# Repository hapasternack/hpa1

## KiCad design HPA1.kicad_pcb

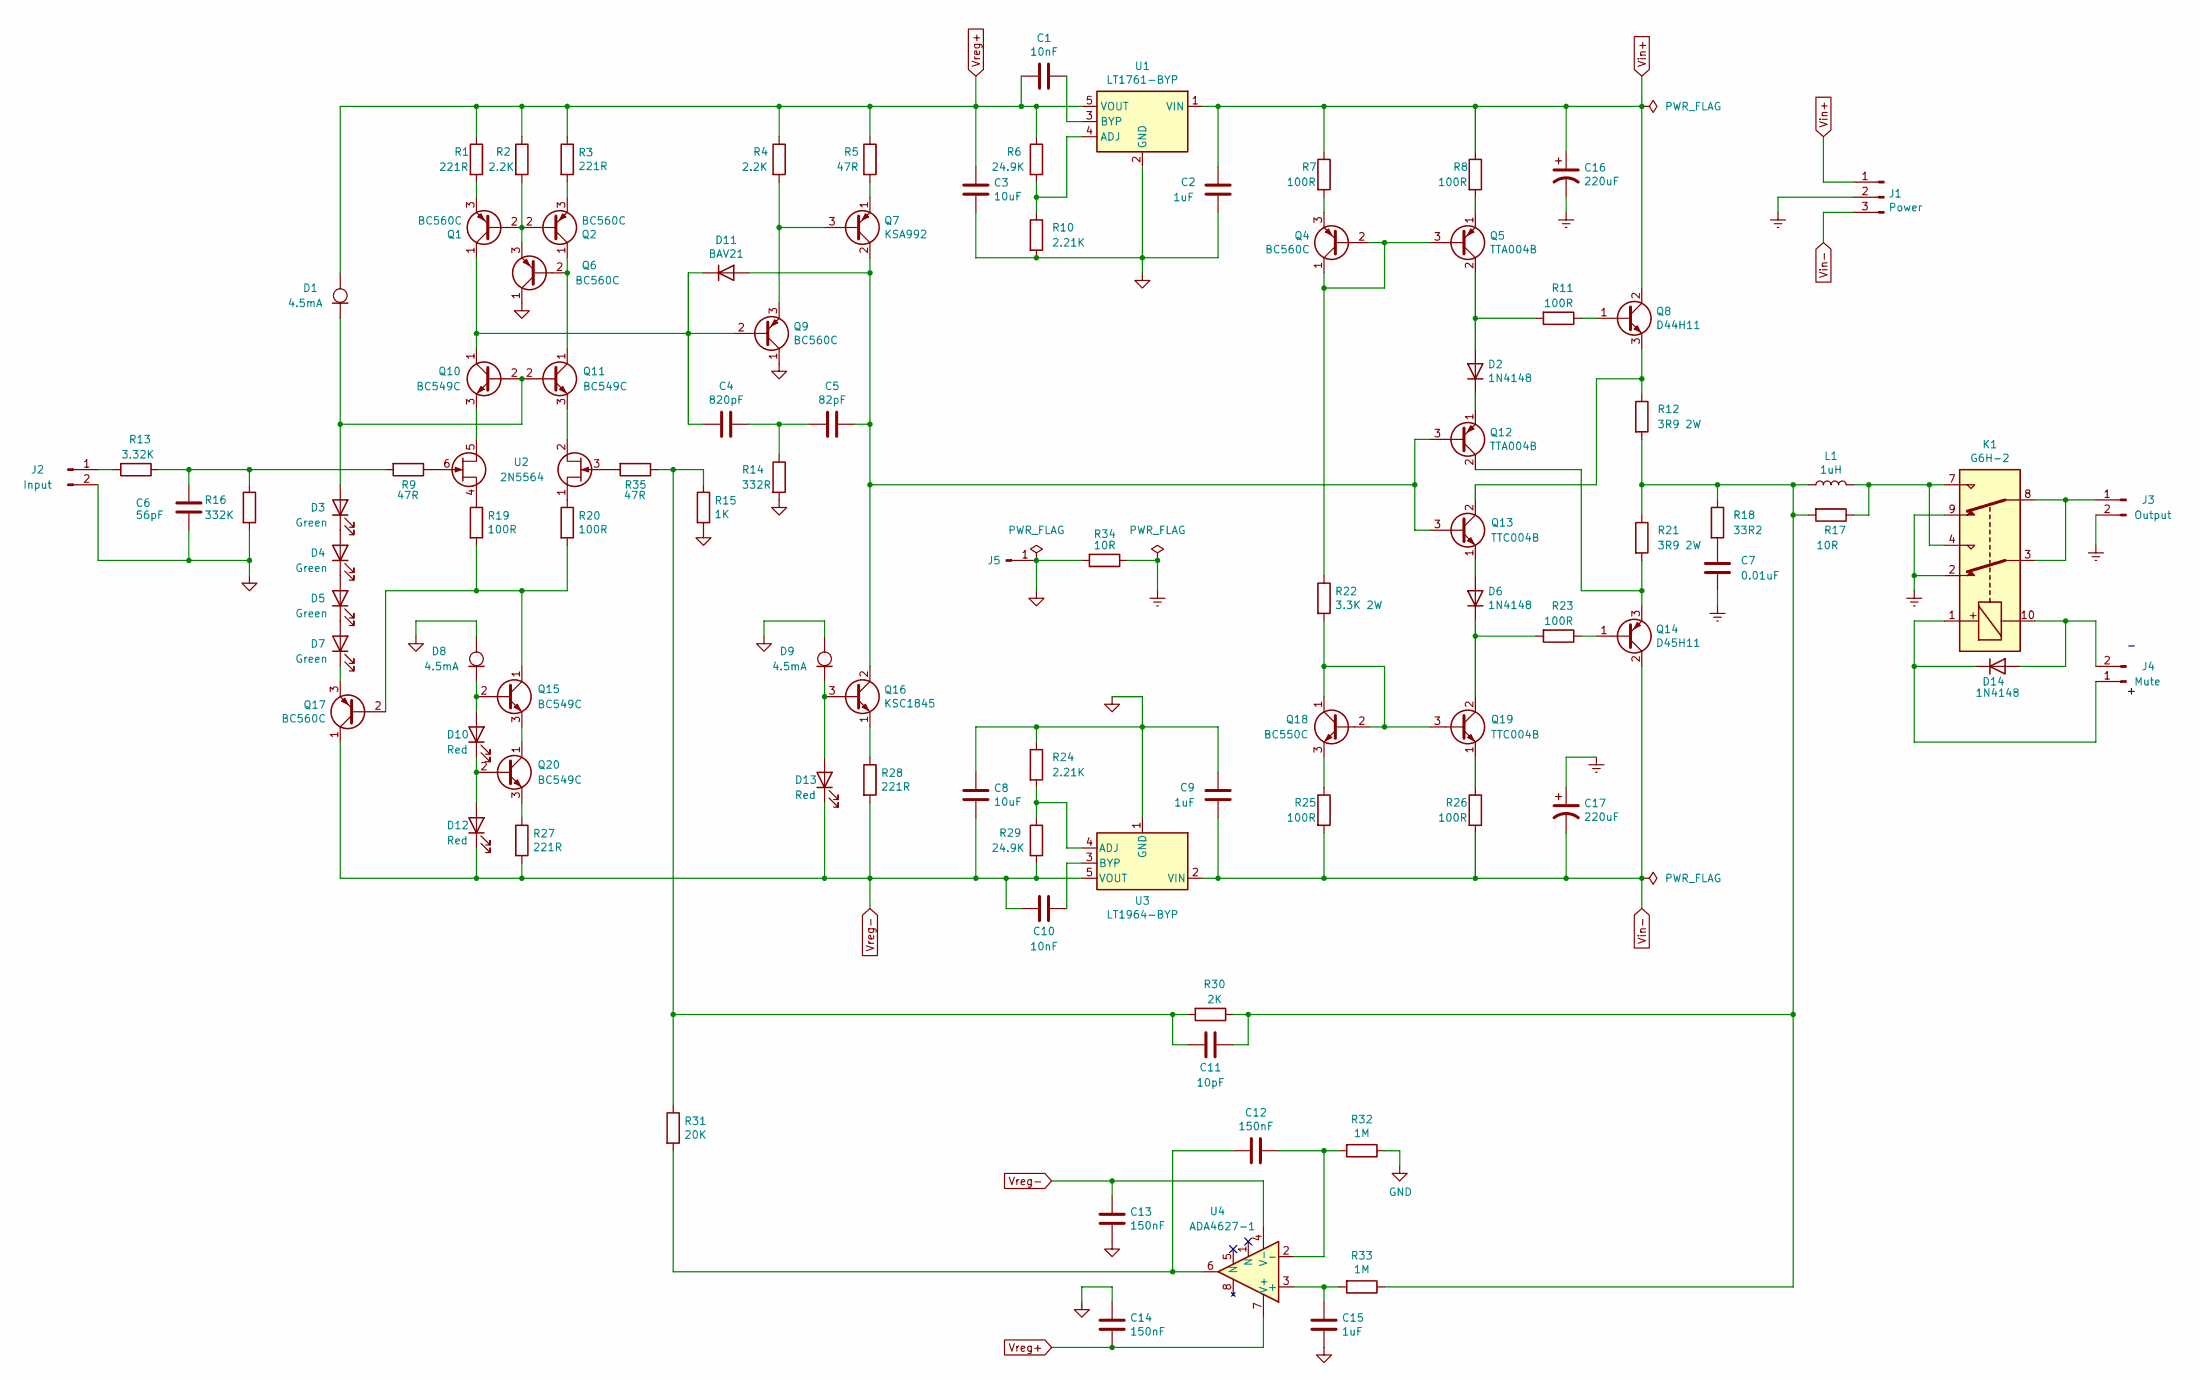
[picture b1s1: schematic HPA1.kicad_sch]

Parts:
C1, C10: 10nF; C_0805_2012Metric_Pad1.18x1.45mm_HandSolder
C2, C9: 1uF; C_1206_3216Metric_Pad1.33x1.80mm_HandSolder
C3, C8: 10uF; C_1206_3216Metric_Pad1.33x1.80mm_HandSolder
C4: 820pF; C_Disc_D3.8mm_W2.6mm_P2.50mm
C5: 82pF; C_Disc_D3.8mm_W2.6mm_P2.50mm
C6: 56pF; C_Disc_D3.8mm_W2.6mm_P2.50mm
C7: 0.01uF; C_Disc_D4.7mm_W2.5mm_P5.00mm
C11: 10pF; C_Disc_D3.8mm_W2.6mm_P2.50mm
C12, C13, C14: 150nF; C_Rect_L7.2mm_W2.5mm_P5.00mm_FKS2_FKP2_MKS2_MKP2
C15: 1uF; C_Rect_L7.2mm_W5.5mm_P5.00mm_FKS2_FKP2_MKS2_MKP2
C16, C17: 220uF; CP_Radial_D10.0mm_P5.00mm
D1, D8, D9: 4.5mA; D_DO-35_SOD27_P7.62mm_Horizontal
D2, D6, D14: 1N4148; D_DO-35_SOD27_P7.62mm_Horizontal
D3, D4, D5, D7: Green; LED_D3.0mm
D10, D12, D13: Red; LED_D3.0mm
D11: BAV21; D_DO-35_SOD27_P7.62mm_Horizontal
J1: Power; 3-pad-wire-connector-22-ga
J2: Input; 2-pad-wire-connector-22-ga
J3: Output; 2-pad-wire-connector-22-ga
J4: Mute; 2-pad-wire-connector-22-ga
J5: Conn_01x01_Male; 1-pad-wire-connector-22-ga
K1: G6H-2; Relay_DPDT_Omron_G6H-2
L1: 1uH; HPA-Output-Coil
Q1, Q2, Q4, Q6, Q9, Q17: BC560C; TO-92_Inline
Q5, Q12: TTA004B; TO-126-3_Vertical
Q7: KSA992; TO-92_Inline
Q8: D44H11; TO-220-3_Vertical
Q10, Q11, Q15, Q20: BC549C; TO-92_Inline
Q13, Q19: TTC004B; TO-126-3_Vertical
Q14: D45H11; TO-220-3_Vertical
Q16: KSC1845; TO-92_Inline
Q18: BC550C; TO-92_Inline
R1, R3, R27, R28: 221R; R_Axial_DIN0207_L6.3mm_D2.5mm_P10.16mm_Horizontal
R2, R4: 2.2K; R_Axial_DIN0207_L6.3mm_D2.5mm_P10.16mm_Horizontal
R5: 47R; R_Axial_DIN0207_L6.3mm_D2.5mm_P10.16mm_Horizontal
R6, R29: 24.9K; R_0805_2012Metric_Pad1.15x1.40mm_HandSolder
R7, R8, R11, R19, R20, R23, R25, R26: 100R; R_Axial_DIN0207_L6.3mm_D2.5mm_P10.16mm_Horizontal
R9, R35: 47R; R_1206_3216Metric
R10, R24: 2.21K; R_0805_2012Metric_Pad1.15x1.40mm_HandSolder
R12, R21: 3R9 2W; R_Axial_DIN0411_L9.9mm_D3.6mm_P12.70mm_Horizontal
R13: 3.32K; R_Axial_DIN0207_L6.3mm_D2.5mm_P10.16mm_Horizontal
R14: 332R; R_Axial_DIN0207_L6.3mm_D2.5mm_P10.16mm_Horizontal
R15: 1K; R_Axial_DIN0207_L6.3mm_D2.5mm_P10.16mm_Horizontal
R16: 332K; R_Axial_DIN0207_L6.3mm_D2.5mm_P10.16mm_Horizontal
R17, R34: 10R; R_Axial_DIN0207_L6.3mm_D2.5mm_P10.16mm_Horizontal
R18: 33R2; R_Axial_DIN0207_L6.3mm_D2.5mm_P10.16mm_Horizontal
R22: 3.3K 2W; R_Axial_DIN0411_L9.9mm_D3.6mm_P12.70mm_Horizontal
R30: 2K; R_Axial_DIN0207_L6.3mm_D2.5mm_P10.16mm_Horizontal
R31: 20K; R_Axial_DIN0207_L6.3mm_D2.5mm_P10.16mm_Horizontal
R32, R33: 1M; R_0805_2012Metric_Pad1.15x1.40mm_HandSolder
U1: LT1761-BYP; TSOT-23-5
U2: 2N5564; TO-71-6
U3: LT1964-BYP; TSOT-23-5
U4: ADA4627-1; SOIC-8_3.9x4.9mm_P1.27mm

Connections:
GND: C2.2, C3.2, C6.2, C8.1, C9.2, C13.2, C14.1, C15.2, D8.2 (A), D9.2 (A), J2.2, J5.1, Q6.1 (C), Q9.1 (C), R10.2, R14.2, R15.2, R16.2, R24.1, R32.1, R34.2, U1.2 (GND), U3.1 (GND)
GNDREF: C7.2, C16.2, C17.1, J1.2, J3.2, K1.2, K1.9, R34.1
unnamed: C4.1, C5.2, R14.1
unnamed: C6.1, R9.2, R13.1, R16.1
unnamed: C7.1, R18.2
unnamed: C11.1, L1.2, R12.2, R17.2, R18.1, R21.1, R30.1, R33.1
unnamed: C11.2, R15.1, R30.2, R31.1, R35.1
unnamed: C12.2, R31.2, U4.6
unnamed: D1.1 (K), D3.2 (A), Q10.2 (B), Q11.2 (B)
unnamed: D2.2 (A), Q5.2 (C), R11.2
unnamed: D2.1 (K), Q12.1 (E)
unnamed: D3.1 (K), D4.2 (A)
unnamed: D4.1 (K), D5.2 (A)
unnamed: D5.1 (K), D7.2 (A)
unnamed: D6.2 (A), Q13.1 (E)
unnamed: D6.1 (K), Q19.2 (C), R23.2
unnamed: D7.1 (K), Q17.3 (E)
unnamed: D8.1 (K), D10.2 (A), Q15.2 (B)
unnamed: D10.1 (K), D12.2 (A), Q20.2 (B)
unnamed: C5.1, D11.2 (A), Q7.2 (C), Q12.3 (B), Q13.3 (B), Q16.2 (C)
unnamed: C4.2, D11.1 (K), Q1.1 (C), Q9.2 (B), Q10.1 (C)
unnamed: D9.1 (K), D13.2 (A), Q16.3 (B)
unnamed: D14.2 (A), J4.2, K1.10
unnamed: D14.1 (K), J4.1, K1.1
unnamed: J2.1, R13.2
unnamed: J3.1, K1.3, K1.8
unnamed: K1.4, K1.7, L1.1, R17.1
unnamed: Q1.2 (B), Q2.2 (B), Q6.3 (E), R2.2
unnamed: Q1.3 (E), R1.2
unnamed: Q2.3 (E), R3.2
unnamed: Q4.1 (C), Q4.2 (B), Q5.3 (B), R22.1
unnamed: Q4.3 (E), R7.2
unnamed: Q5.1 (E), R8.2
unnamed: Q7.3 (B), Q9.3 (E), R4.2
unnamed: Q7.1 (E), R5.2
unnamed: Q8.1 (B), R11.1
unnamed: Q10.3 (E), U2.5 (2D)
unnamed: Q2.1 (C), Q6.2 (B), Q11.1 (C)
unnamed: Q11.3 (E), U2.2 (1D)
unnamed: Q12.2 (C), Q14.3 (E), R21.2
unnamed: Q8.3 (E), Q13.2 (C), R12.1
unnamed: Q14.1 (B), R23.1
unnamed: Q15.1 (C), Q17.2 (B), R19.2, R20.2
unnamed: Q15.3 (E), Q20.1 (C)
unnamed: Q16.1 (E), R28.1
unnamed: Q18.1 (C), Q18.2 (B), Q19.3 (B), R22.2
unnamed: Q18.3 (E), R25.1
unnamed: Q19.1 (E), R26.1
unnamed: Q20.3 (E), R27.1
unnamed: R6.2, R10.1, U1.4 (ADJ)
unnamed: C1.1, U1.3 (BYP)
unnamed: R35.2, U2.3 (1G)
unnamed: R20.1, U2.1 (1S)
unnamed: R9.1, U2.6 (2G)
unnamed: R19.1, U2.4 (2S)
unnamed: R24.2, R29.1, U3.4 (ADJ)
unnamed: C10.1, U3.3 (BYP)
unnamed: C15.1, R33.2, U4.3 (+)
unnamed: C12.1, R32.2, U4.2 (-)
Vin+: C2.1, C16.1, J1.1, Q8.2 (C), R7.1, R8.1, U1.1 (VIN)
Vin-: C9.1, C17.2, J1.3, Q14.2 (C), R25.2, R26.2, U3.2 (VIN)
Vreg+: C1.2, C3.1, C14.2, D1.2 (A), R1.1, R2.1, R3.1, R4.1, R5.1, R6.1, U1.5 (VOUT), U4.7 (V+)
Vreg-: C8.2, C10.2, C13.1, D12.1 (K), D13.1 (K), Q17.1 (C), R27.2, R28.2, R29.2, U3.5 (VOUT), U4.4 (V-)

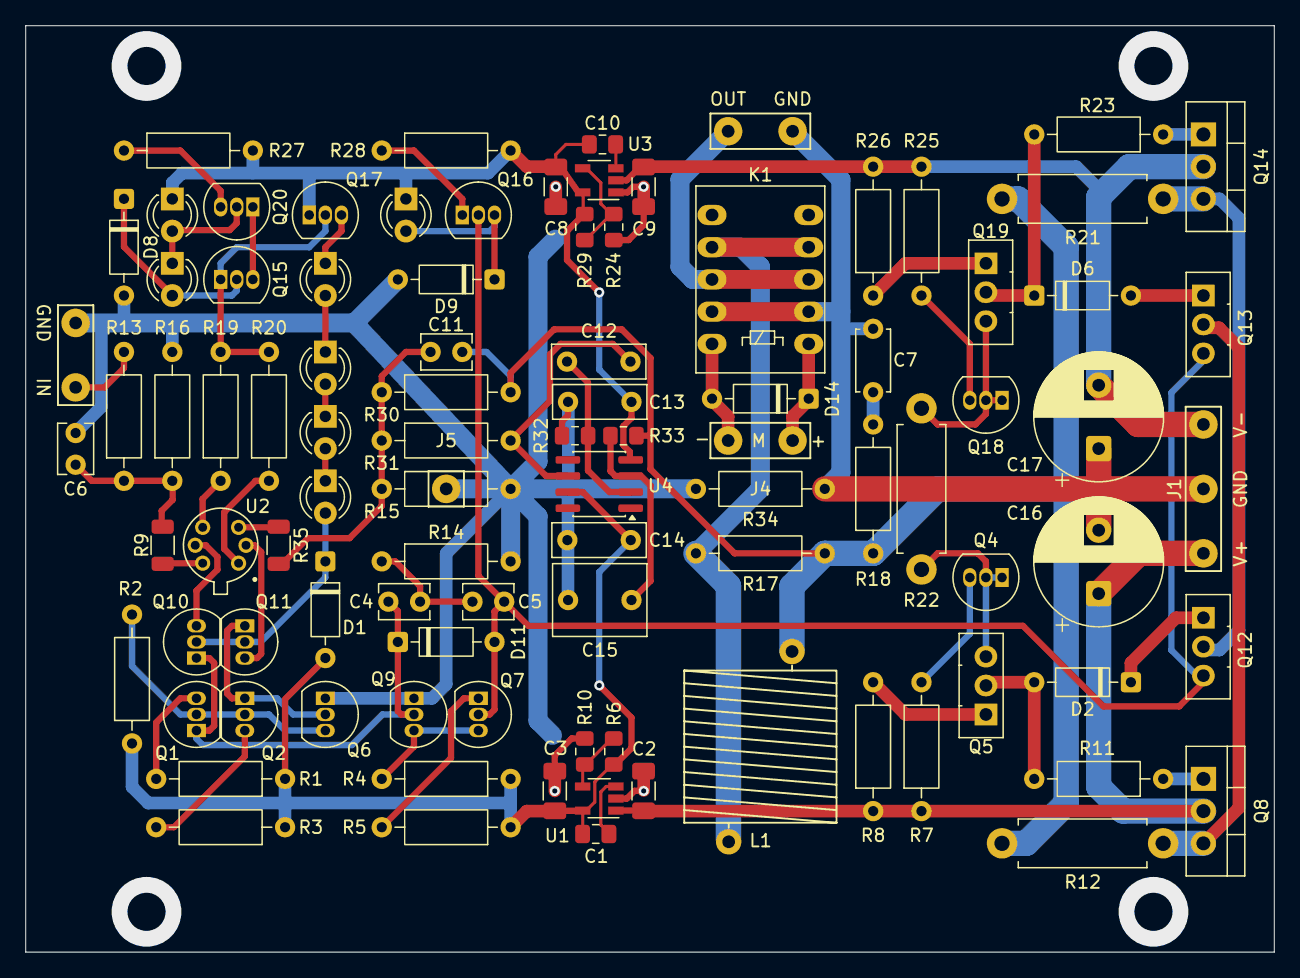
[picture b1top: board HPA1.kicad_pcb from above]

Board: 2 copper layers, 98.4 x 73.0 mm, 96 parts (0 on the bottom side), 63 nets.

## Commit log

2025-11-06 Converted to KiCad 9.0.
2026-03-09 Created local symbol and footprint libraries. Updated schematic and PCB. Fixed all rule check errors.
